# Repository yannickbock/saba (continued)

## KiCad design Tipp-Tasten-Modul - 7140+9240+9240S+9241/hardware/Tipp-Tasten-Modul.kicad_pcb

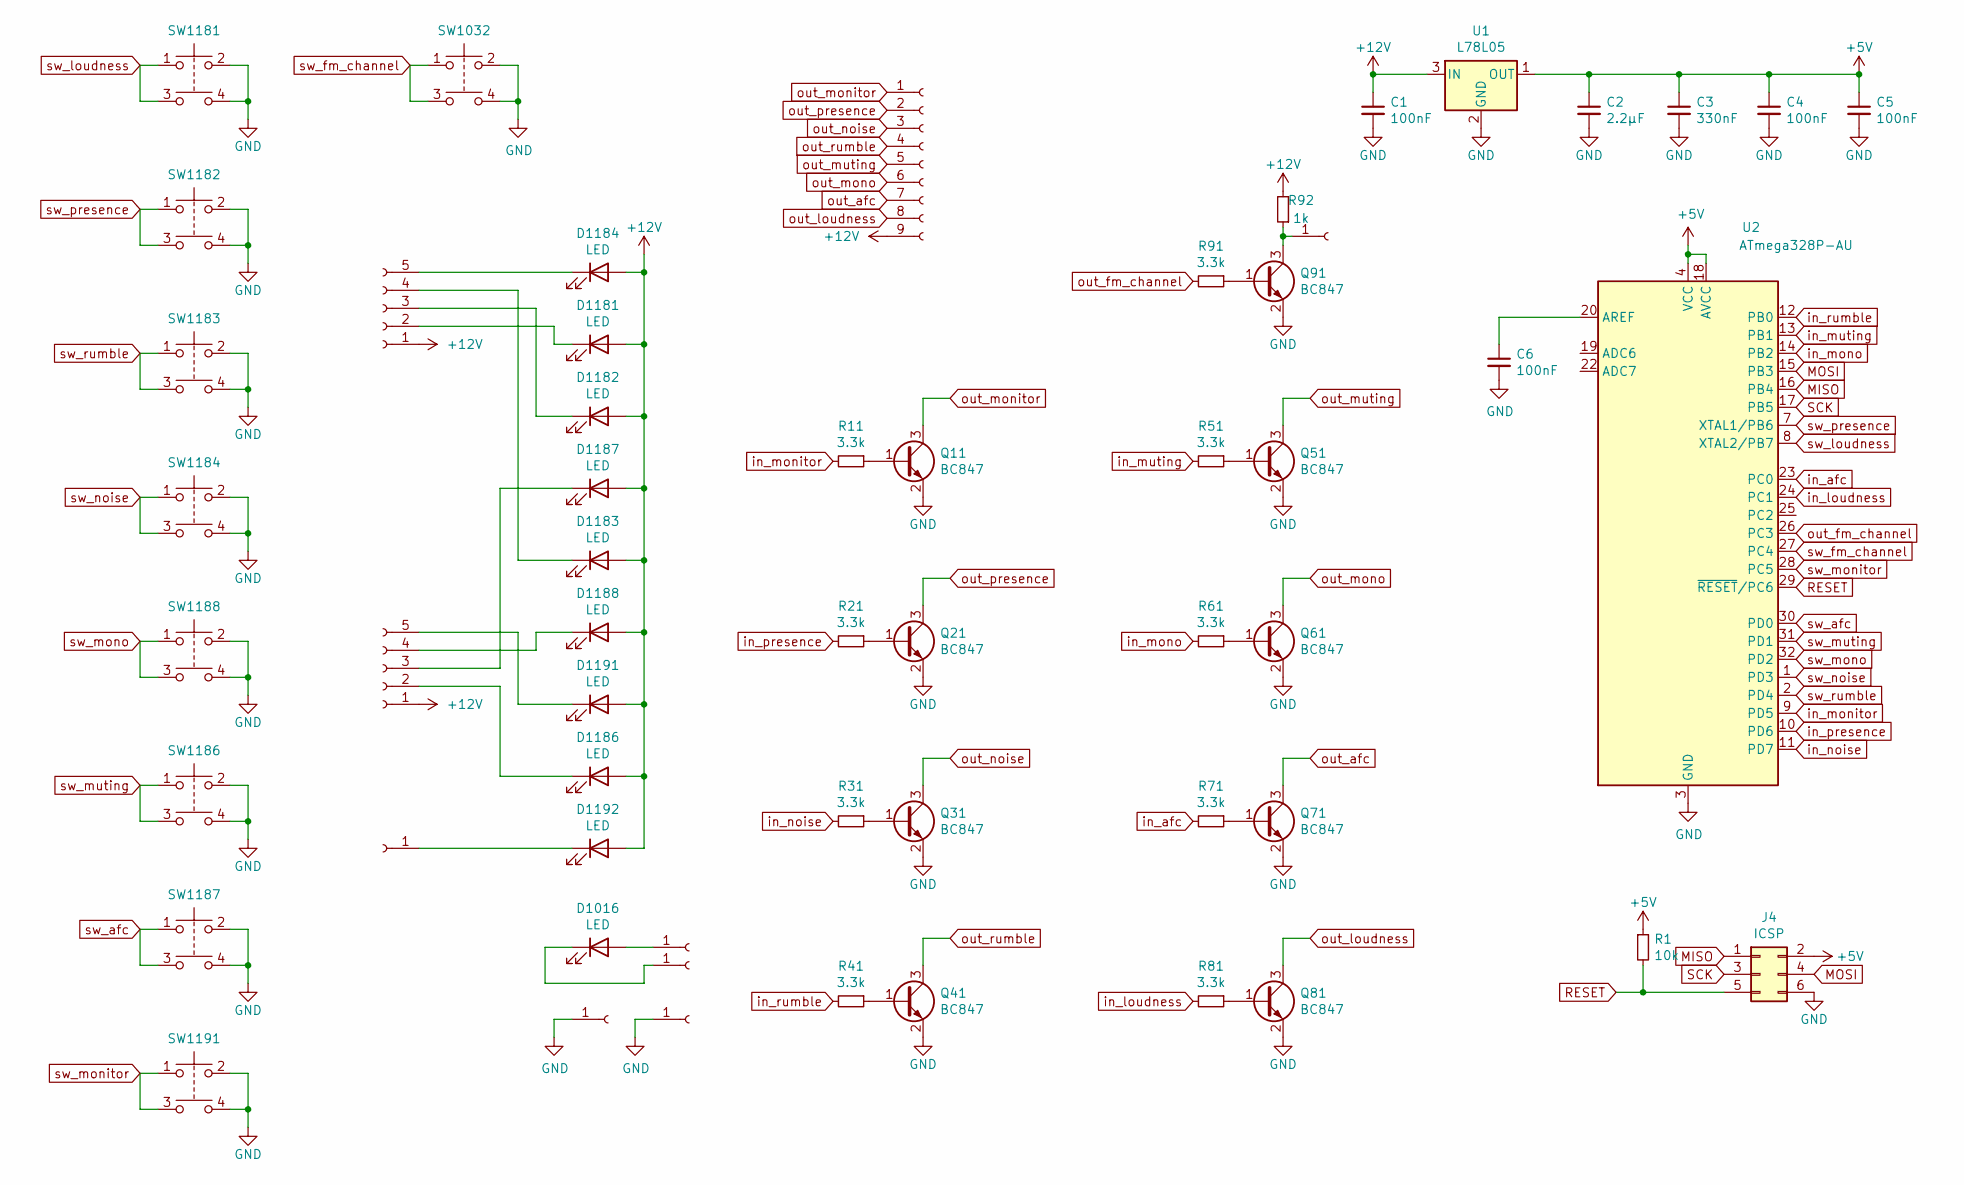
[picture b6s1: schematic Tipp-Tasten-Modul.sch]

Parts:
C1, C4, C5, C6: 100nF; C_0805; LCSC C49678
C2: 2.2µF; C_0805; LCSC C49217
C3: 330nF; C_0805; LCSC C1740
D1016: LED; LED_D5.0mm
D1181, D1182, D1183, D1184, D1186, D1187, D1188, D1191, D1192: LED; LED_D3.0mm
J1: Conn_01x09_Female; SolderWirePad_09_2.54mm
J2, J3: Conn_01x05_Female; SolderWirePad_05_2.54mm
J4: ICSP; Pin_Header_Straight_2x03_Pitch2.54mm
J5, J6, J7, J8, J9, J10: Conn_01x01_Female; SolderWirePad_single_1-5mmDrill
Q11, Q21, Q31, Q41, Q51, Q61, Q71, Q81, Q91: BC847; SOT-23; LCSC C2146
R1: 10k; R_0805; LCSC C17414
R11, R21, R31, R41, R51, R61, R71, R81, R91: 3.3k; R_0805; LCSC C26010
R92: 1k; R_0805; LCSC C17513
SW1032: SW_Push_Dual; saba_92xx_push_button
SW1181, SW1182, SW1183, SW1184, SW1186, SW1187, SW1188, SW1191: SW_Push_Dual; SW_PUSH_DPDT
U1: L78L05; SOT-89-3; LCSC C71136
U2: ATmega328P-AU; TQFP-32_7x7mm_Pitch0.8mm; LCSC C14877

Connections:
+5V: C2.1, C3.1, C4.1, C5.1, J4.2, R1.1, U1.1 (OUT), U2.4 (VCC), U2.6 (VCC), U2.18 (AVCC)
+12V: C1.1, D1181.2 (A), D1182.2 (A), D1183.2 (A), D1184.2 (A), D1186.2 (A), D1187.2 (A), D1188.2 (A), D1191.2 (A), D1192.2 (A), J1.9, J2.1, J3.1, R92.2, U1.3 (IN)
GND: C1.2, C2.2, C3.2, C4.2, C5.2, C6.2, J4.6, J6.1, J9.1, Q11.2 (E), Q21.2 (E), Q31.2 (E), Q41.2 (E), Q51.2 (E), Q61.2 (E), Q71.2 (E), Q81.2 (E), Q91.2 (E), SW1032.2, SW1032.4, SW1181.2, SW1181.4, SW1182.2, SW1182.4, SW1183.2, SW1183.4, SW1184.2, SW1184.4, SW1186.2, SW1186.4, SW1187.2, SW1187.4, SW1188.2, SW1188.4, SW1191.2, SW1191.4, U1.2 (GND), U2.3 (GND), U2.5 (GND), U2.21 (GND)
MISO: J4.1, U2.16 (PB4)
MOSI: J4.4, U2.15 (PB3)
unnamed: C6.1, U2.20 (AREF)
unnamed: D1016.1 (K), J10.1
unnamed: D1016.2 (A), J5.1
unnamed: D1181.1 (K), J3.2
unnamed: D1182.1 (K), J3.3
unnamed: D1183.1 (K), J3.4
unnamed: D1184.1 (K), J3.5
unnamed: D1186.1 (K), J2.2
unnamed: D1187.1 (K), J2.3
unnamed: D1188.1 (K), J2.4
unnamed: D1191.1 (K), J2.5
unnamed: D1192.1 (K), J8.1
unnamed: J7.1, Q91.3 (C), R92.1
unnamed: Q11.1 (B), R11.1
unnamed: Q21.1 (B), R21.1
unnamed: Q31.1 (B), R31.1
unnamed: Q41.1 (B), R41.1
unnamed: Q51.1 (B), R51.1
unnamed: Q61.1 (B), R61.1
unnamed: Q71.1 (B), R71.1
unnamed: Q81.1 (B), R81.1
unnamed: Q91.1 (B), R91.1
RESET: J4.5, R1.2, U2.29 (~RESET~/PC6)
SCK: J4.3, U2.17 (PB5)
in_afc: R71.2, U2.23 (PC0)
in_loudness: R81.2, U2.24 (PC1)
in_monitor: R11.2, U2.9 (PD5)
in_mono: R61.2, U2.14 (PB2)
in_muting: R51.2, U2.13 (PB1)
in_noise: R31.2, U2.11 (PD7)
in_presence: R21.2, U2.10 (PD6)
in_rumble: R41.2, U2.12 (PB0)
out_afc: J1.7, Q71.3 (C)
out_fm_channel: R91.2, U2.26 (PC3)
out_loudness: J1.8, Q81.3 (C)
out_monitor: J1.1, Q11.3 (C)
out_mono: J1.6, Q61.3 (C)
out_muting: J1.5, Q51.3 (C)
out_noise: J1.3, Q31.3 (C)
out_presence: J1.2, Q21.3 (C)
out_rumble: J1.4, Q41.3 (C)
sw_afc: SW1187.1, SW1187.3, U2.30 (PD0)
sw_fm_channel: SW1032.1, SW1032.3, U2.27 (PC4)
sw_loudness: SW1181.1, SW1181.3, U2.8 (XTAL2/PB7)
sw_monitor: SW1191.1, SW1191.3, U2.28 (PC5)
sw_mono: SW1188.1, SW1188.3, U2.32 (PD2)
sw_muting: SW1186.1, SW1186.3, U2.31 (PD1)
sw_noise: SW1184.1, SW1184.3, U2.1 (PD3)
sw_presence: SW1182.1, SW1182.3, U2.7 (XTAL1/PB6)
sw_rumble: SW1183.1, SW1183.3, U2.2 (PD4)

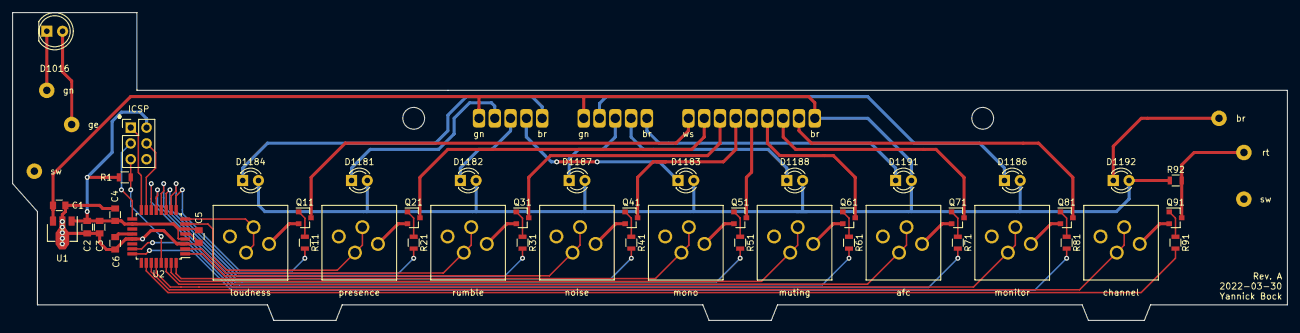
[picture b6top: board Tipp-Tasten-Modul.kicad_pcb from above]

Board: 2 copper layers, 205.0 x 49.5 mm, 59 parts (0 on the bottom side), 55 nets.

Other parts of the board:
M2, M3: MountingHole_3.5mm
